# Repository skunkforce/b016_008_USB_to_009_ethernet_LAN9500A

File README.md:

# edgy_board number b016
This design is part of the [edgy board project](https://github.com/skunkforce/edgy_boards).

# getting started
This repository uses submodules. After cloning use the command 

```$ git submodule update --init --recursive```

to pull the submodules before opening the project with kicad. 

# Tests
Tests can be found in [TESTS.md](TESTS.md)

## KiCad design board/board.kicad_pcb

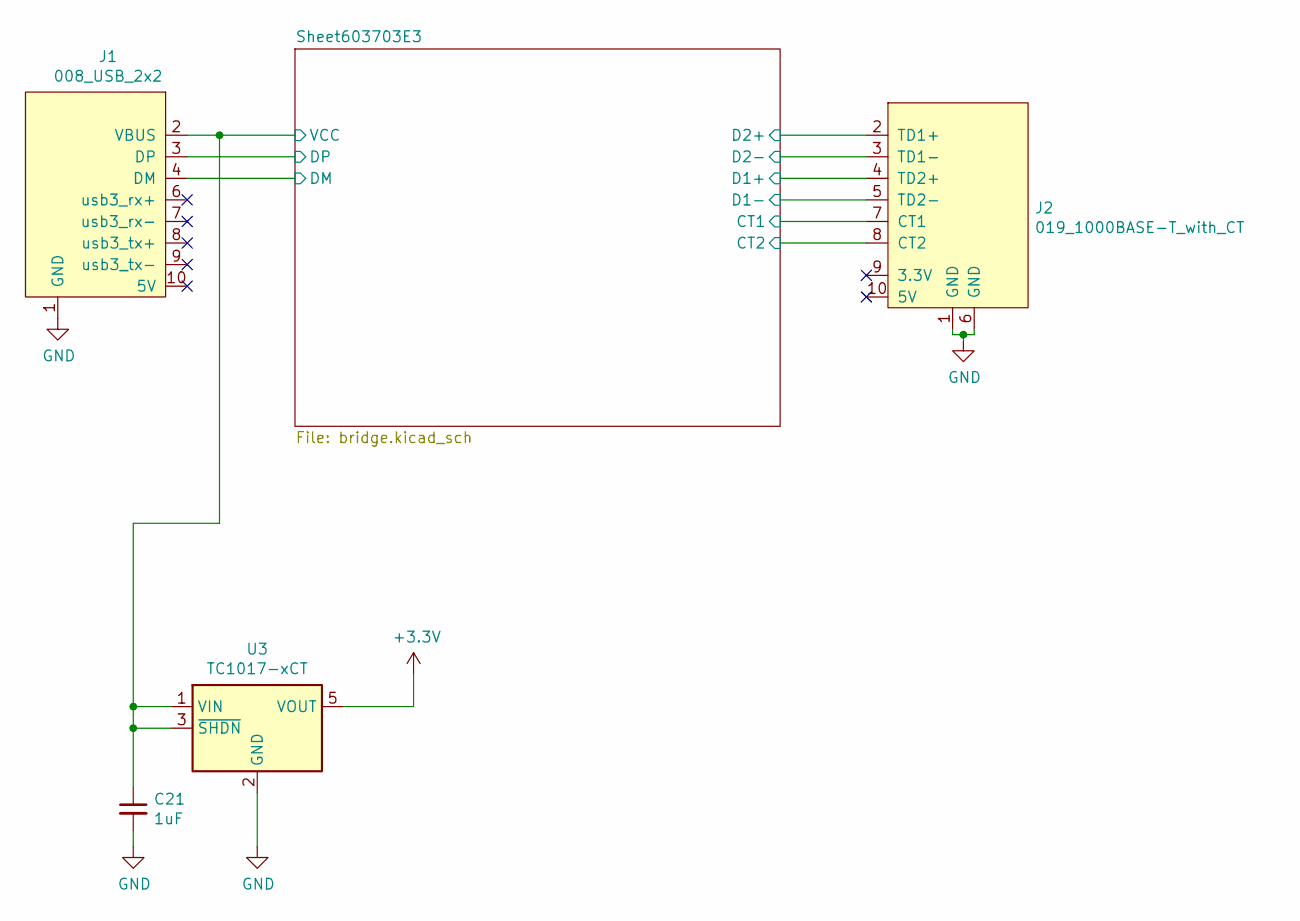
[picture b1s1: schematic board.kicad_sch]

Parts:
C21: 1uF; C_0603_1608Metric
J1: 008_USB_2x2; on_edge_2x05_device
J2: 019_1000BASE-T_with_CT; on_edge_2x05_host
U3: TC1017-xCT; SOT-23-5

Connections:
+3.3V: U3.5 (VOUT); also elsewhere on the board
/Sheet603703E3/CT1: J2.7 (CT1), J2.8 (CT2); also elsewhere on the board
/Sheet603703E3/D1+: J2.4 (TD2+); also elsewhere on the board
/Sheet603703E3/D1-: J2.5 (TD2-); also elsewhere on the board
/Sheet603703E3/D2+: J2.2 (TD1+); also elsewhere on the board
/Sheet603703E3/D2-: J2.3 (TD1-); also elsewhere on the board
/Sheet603703E3/DM: J1.4 (DM); also elsewhere on the board
/Sheet603703E3/DP: J1.3 (DP); also elsewhere on the board
/VCC: C21.1, J1.2 (VBUS), U3.1 (VIN), U3.3 (~SHDN)
GND: C21.2, J1.1 (GND), J2.1 (GND), J2.6 (GND), U3.2 (GND); also elsewhere on the board

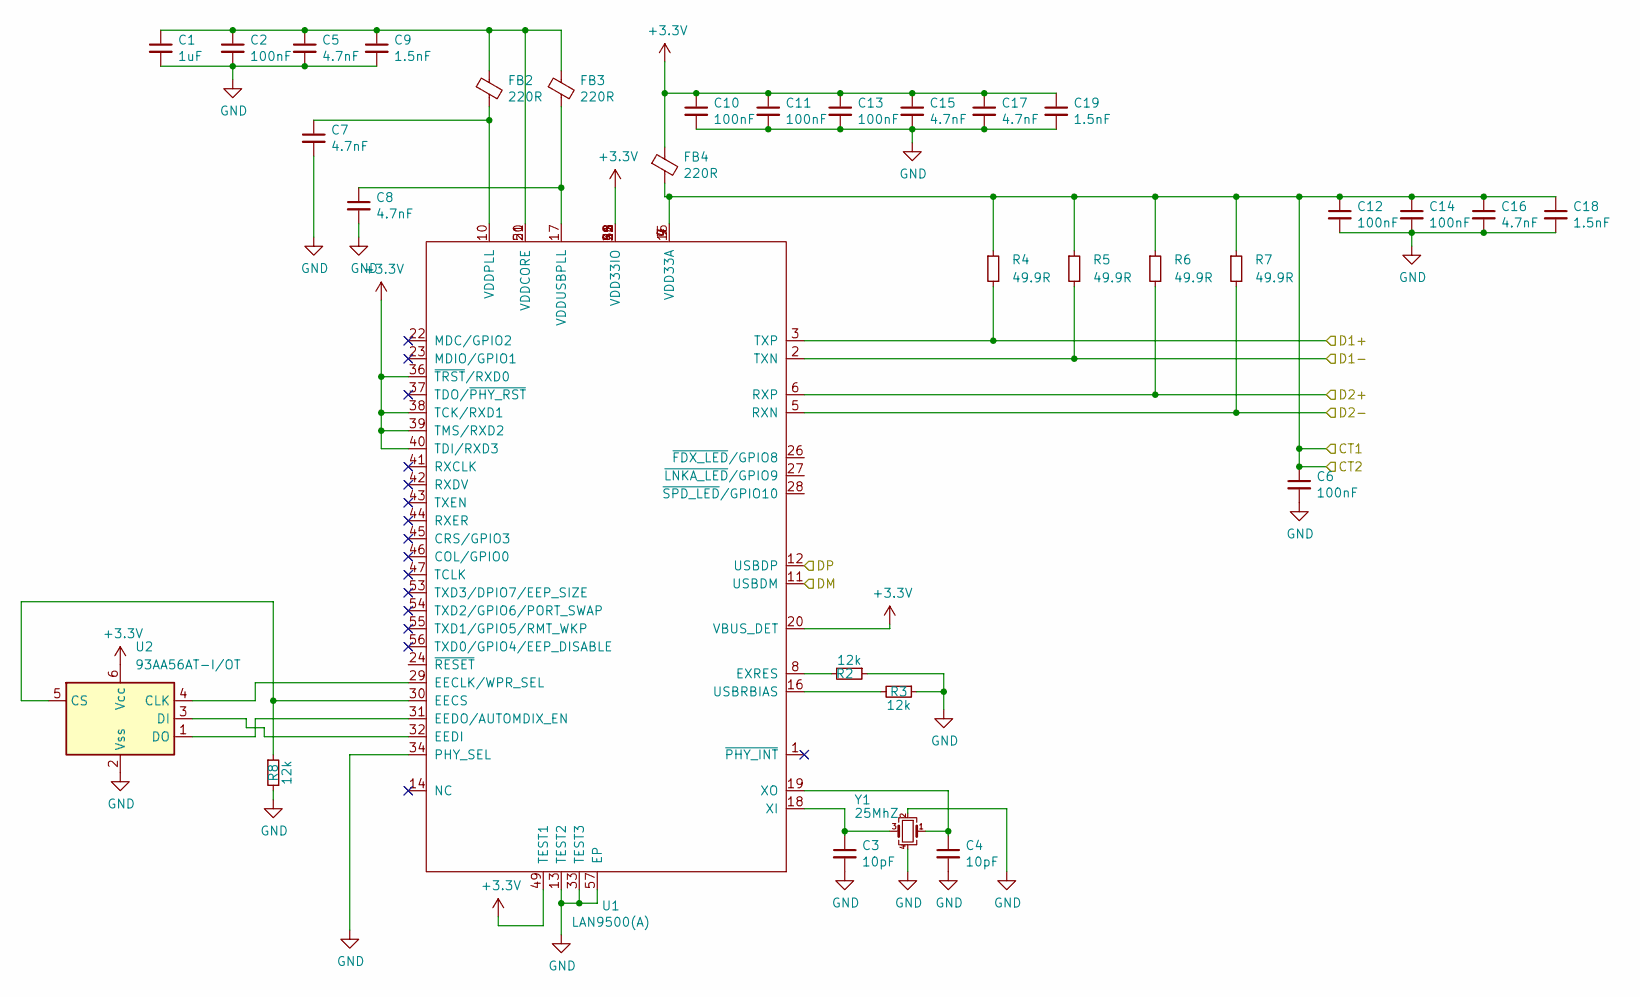
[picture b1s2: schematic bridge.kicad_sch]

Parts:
C1: 1uF; C_0603_1608Metric
C2, C6, C10, C11, C12, C13, C14: 100nF; C_0603_1608Metric
C3, C4: 10pF; C_0603_1608Metric
C5, C7, C8, C15, C16, C17: 4.7nF; C_0603_1608Metric
C9, C18, C19: 1.5nF; C_0603_1608Metric
FB2, FB3, FB4: 220R; L_0805_2012Metric
R2, R3, R8: 12k; R_0603_1608Metric
R4, R5, R6, R7: 49.9R; R_0603_1608Metric
U1: LAN9500(A); QFN-56-1EP_8x8mm_P0.5mm_EP4.5x5.2mm; MPN LAN9500A
U2: 93AA56AT-I/OT; SOT-23-6
Y1: 25MhZ; Crystal_SMD_Abracon_ABM8G-4Pin_3.2x2.5mm; MPN 535-9140-1-ND

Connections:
+3.3V: C10.1, C11.1, C13.1, C15.1, C17.1, C19.1, FB4.1, U1.20 (VBUS_DET), U1.25 (VDD33IO), U1.35 (VDD33IO), U1.36 (~TRST/RXD0), U1.38 (TCK/RXD1), U1.39 (TMS/RXD2), U1.40 (TDI/RXD3), U1.48 (VDD33IO), U1.49 (TEST1), U1.51 (VDD33IO), U1.52 (VDD33IO), U2.6 (Vcc); also elsewhere on the board
/Sheet603703E3/CT1: C6.1, C12.1, C14.1, C16.1, C18.1, FB4.2, R4.1, R5.1, R6.1, R7.1, U1.4 (VDD33A), U1.7 (VDD33A), U1.9 (VDD33A), U1.15 (VDD33A); also elsewhere on the board
/Sheet603703E3/D1+: R4.2, U1.3 (TXP); also elsewhere on the board
/Sheet603703E3/D1-: R5.2, U1.2 (TXN); also elsewhere on the board
/Sheet603703E3/D2+: R6.2, U1.6 (RXP); also elsewhere on the board
/Sheet603703E3/D2-: R7.2, U1.5 (RXN); also elsewhere on the board
/Sheet603703E3/DM: U1.11 (USBDM); also elsewhere on the board
/Sheet603703E3/DP: U1.12 (USBDP); also elsewhere on the board
GND: C1.2, C2.2, C3.2, C4.2, C5.2, C6.2, C7.2, C8.2, C9.2, C10.2, C11.2, C12.2, C13.2, C14.2, C15.2, C16.2, C17.2, C18.2, C19.2, R2.1, R3.1, R8.2, U1.13 (TEST2), U1.33 (TEST3), U1.34 (PHY_SEL), U1.57 (EP), U2.2 (Vss), Y1.2, Y1.4; also elsewhere on the board
unnamed: C1.1, C2.1, C5.1, C9.1, FB2.1, FB3.1, U1.21 (VDDCORE), U1.50 (VDDCORE)
unnamed: C3.1, U1.18 (XI), Y1.3
unnamed: C4.1, U1.19 (XO), Y1.1
unnamed: C7.1, FB2.2, U1.10 (VDDPLL)
unnamed: C8.1, FB3.2, U1.17 (VDDUSBPLL)
unnamed: R2.2, U1.8 (EXRES)
unnamed: R3.2, U1.16 (USBRBIAS)
unnamed: R8.1, U1.30 (EECS), U2.5 (CS)
unnamed: U1.29 (EECLK/WPR_SEL), U2.4 (CLK)
unnamed: U1.31 (EEDO/AUTOMDIX_EN), U2.1 (DO)
unnamed: U1.32 (EEDI), U2.3 (DI)

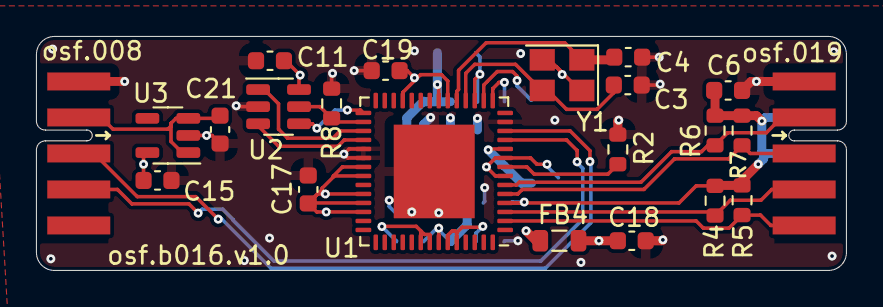
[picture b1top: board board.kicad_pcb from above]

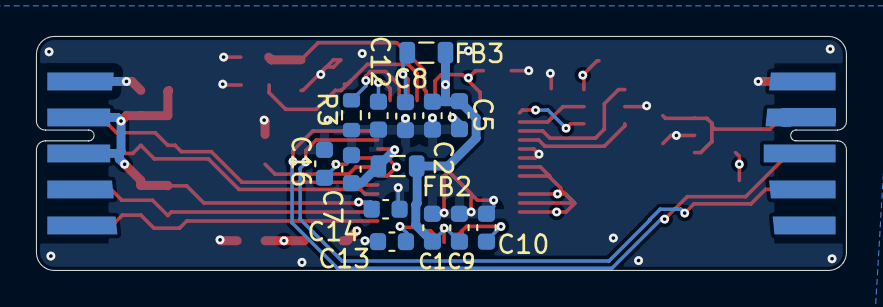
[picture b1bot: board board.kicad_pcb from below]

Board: 4 copper layers, 45.0 x 13.0 mm, 36 parts (14 on the bottom side), 21 nets.

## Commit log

2023-03-18 initial hw
2023-04-19 changed osf.009 to osf.019 on silkscreen
